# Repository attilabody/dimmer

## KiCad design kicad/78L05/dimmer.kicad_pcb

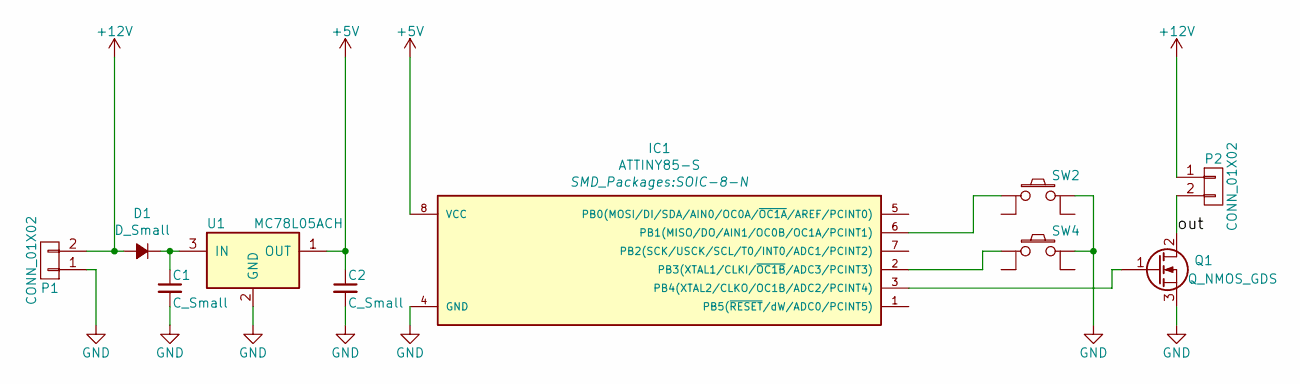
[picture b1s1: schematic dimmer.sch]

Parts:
C1, C2: C_Small; C_0805
D1: D_Small; SMA_Standard
IC1: ATTINY85-S; SOIC-8-N
P1, P2: CONN_01X02; W237-132
Q1: Q_NMOS_GDS; SOT-23_Handsoldering
SW2, SW4: TACTILE_SW; SW_TH_Tactile_Omron_B3F-10xx
U1: MC78L05ACH; SOT89-3_Housing

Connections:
+5V: C2.1, IC1.8 (VCC), U1.1 (OUT)
+12V: D1.2 (A), P1.2, P2.1
/out: P2.2, Q1.2 (D)
GND: C1.2, C2.2, IC1.4 (GND), P1.1, Q1.3 (S), SW2.3, SW4.3, U1.2 (GND)
unnamed: C1.1, D1.1 (K), U1.3 (IN)
unnamed: IC1.2 (PB3(XTAL1/CLKI/~OC1B~/ADC3/PCINT3)), SW4.1
unnamed: IC1.3 (PB4(XTAL2/CLKO/OC1B/ADC2/PCINT4)), Q1.1 (G)
unnamed: IC1.6 (PB1(MISO/DO/AIN1/OC0B/OC1A/PCINT1)), SW2.1

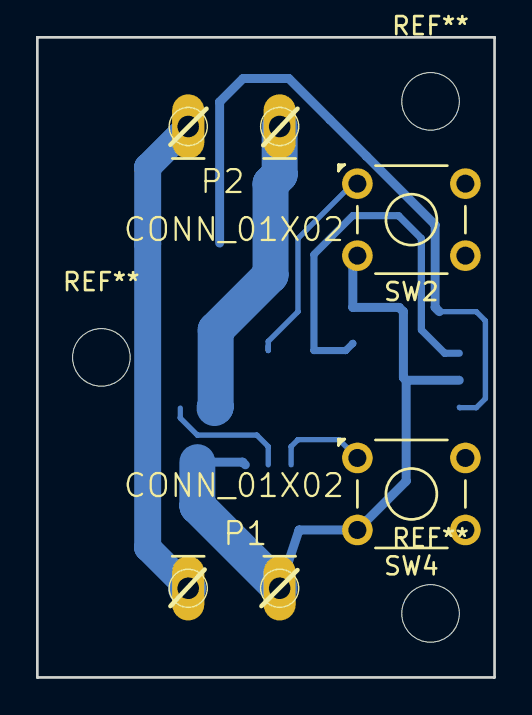
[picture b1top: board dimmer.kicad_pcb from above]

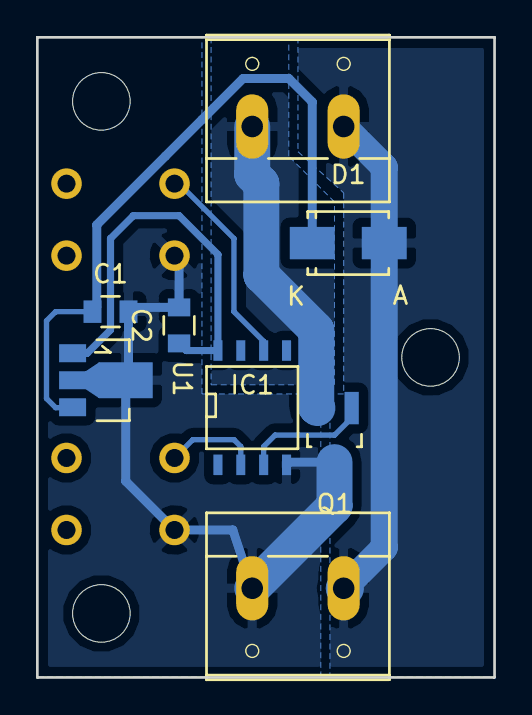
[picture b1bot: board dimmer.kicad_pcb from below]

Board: 2 copper layers, 25.4 x 35.6 mm, 10 parts (6 on the bottom side), 8 nets.

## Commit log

2016-08-10 PushButton working (push, click, doubleclick)
2016-08-11 click will be delayed until doubleclick timeout expires
2016-08-12 pcb progress
2016-08-12 pcb: changing sides
2016-08-13 pcb: proper t85 footprint
2016-08-14 doubleclick memory
2016-08-17 Updated to 230V Dimmer support
2016-10-15 Forking hardware (78L05 vs AMS1117)
2016-10-15 AMS1117-5.0 regulator version
2016-10-15 Atmel studio project fixes
2016-10-15 Project reorganization
2016-10-15 ATtiny85 dimmer: separated button logic, port handling and debouncing
2016-10-15 ButtonLogic fix
2016-10-15 buttontest project reorg
2016-10-15 ButtonLogic && IOPort added
2016-10-15 AMS1117 correct footprint
2016-10-17 AMS117 PCB version: fixed attyny85 footprint
2016-10-18 78L05 PCB: added guard diode
